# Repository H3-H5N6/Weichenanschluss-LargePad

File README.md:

# Beschreibung

Platine, die die Verkabelung vereinfachen kann. Nutzbar, um 12V oder Fahrstrom zu verteilen.

Es können auch mehrere dieser Platinen miteinander verbunden werden.

Auf der Bestückungsseite(Oberseite) liegt der eine Pol oben, der andere oben.

Auf der Unterseite liegen die beiden Pole jeweils nebeneinander.

# Schaltplan

# Bestückungsplan

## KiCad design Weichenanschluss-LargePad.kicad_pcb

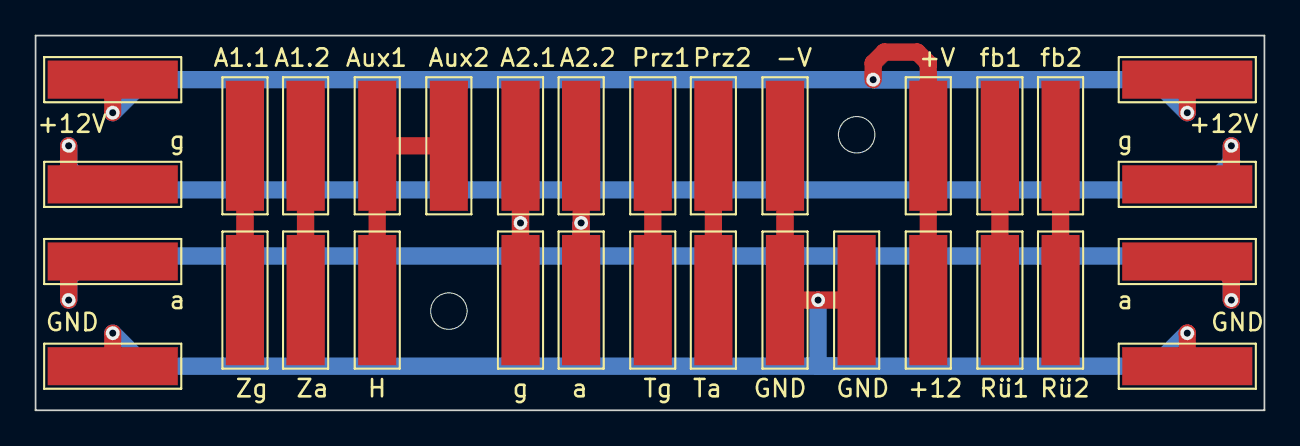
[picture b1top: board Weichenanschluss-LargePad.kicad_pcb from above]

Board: 2 copper layers, 70.8 x 21.6 mm, 36 parts (0 on the bottom side), 11 nets.

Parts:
H1, H3: MountingHole; MountingHole_2.1mm
J1: A1.1; Pad_7.5x2.2mm
J2: A1.2; Pad_7.5x2.2mm
J3: Aux1; Pad_7.5x2.2mm
J4: Aux2; Pad_7.5x2.2mm
J5: A2.1; Pad_7.5x2.2mm
J6: A2.2; Pad_7.5x2.2mm
J7: Prz1; Pad_7.5x2.2mm
J8: Prz2; Pad_7.5x2.2mm
J9: -V; Pad_7.5x2.2mm
J11: +V; Pad_7.5x2.2mm
J12: fb1; Pad_7.5x2.2mm
J13: fb2; Pad_7.5x2.2mm
J21: Zg; Pad_7.5x2.2mm
J22: Za; Pad_7.5x2.2mm
J23: H; Pad_7.5x2.2mm
J25, J41, J51: g; Pad_7.5x2.2mm
J26, J42, J52: a; Pad_7.5x2.2mm
J27: Tg; Pad_7.5x2.2mm
J28: Ta; Pad_7.5x2.2mm
J29, J30, J44, J54: GND; Pad_7.5x2.2mm
J31: +12; Pad_7.5x2.2mm
J32: Rü1; Pad_7.5x2.2mm
J33: Rü2; Pad_7.5x2.2mm
J43, J53: +12V; Pad_7.5x2.2mm
Tx1: ©H3-H5N6; Text
Tx2: Weichenanschluss-LargePad v1.1; Text

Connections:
+12V: J11.1 (Pin_1_1), J31.1 (Pin_1_1), J43.1 (Pin_1_1), J53.1 (Pin_1_1)
GND: J9.1 (Pin_1_1), J29.1 (Pin_1_1), J30.1 (Pin_1_1), J44.1 (Pin_1_1), J54.1 (Pin_1_1)
unnamed: J1.1 (Pin_1_1), J21.1 (Pin_1_1)
unnamed: J2.1 (Pin_1_1), J22.1 (Pin_1_1)
unnamed: J12.1 (Pin_1_1), J32.1 (Pin_1_1)
unnamed: J13.1 (Pin_1_1), J33.1 (Pin_1_1)
unnamed: J3.1 (Pin_1_1), J4.1 (Pin_1_1), J23.1 (Pin_1_1)
unnamed: J5.1 (Pin_1_1), J25.1 (Pin_1_1), J41.1 (Pin_1_1), J51.1 (Pin_1_1)
unnamed: J6.1 (Pin_1_1), J26.1 (Pin_1_1), J42.1 (Pin_1_1), J52.1 (Pin_1_1)
unnamed: J7.1 (Pin_1_1), J27.1 (Pin_1_1)
unnamed: J8.1 (Pin_1_1), J28.1 (Pin_1_1)

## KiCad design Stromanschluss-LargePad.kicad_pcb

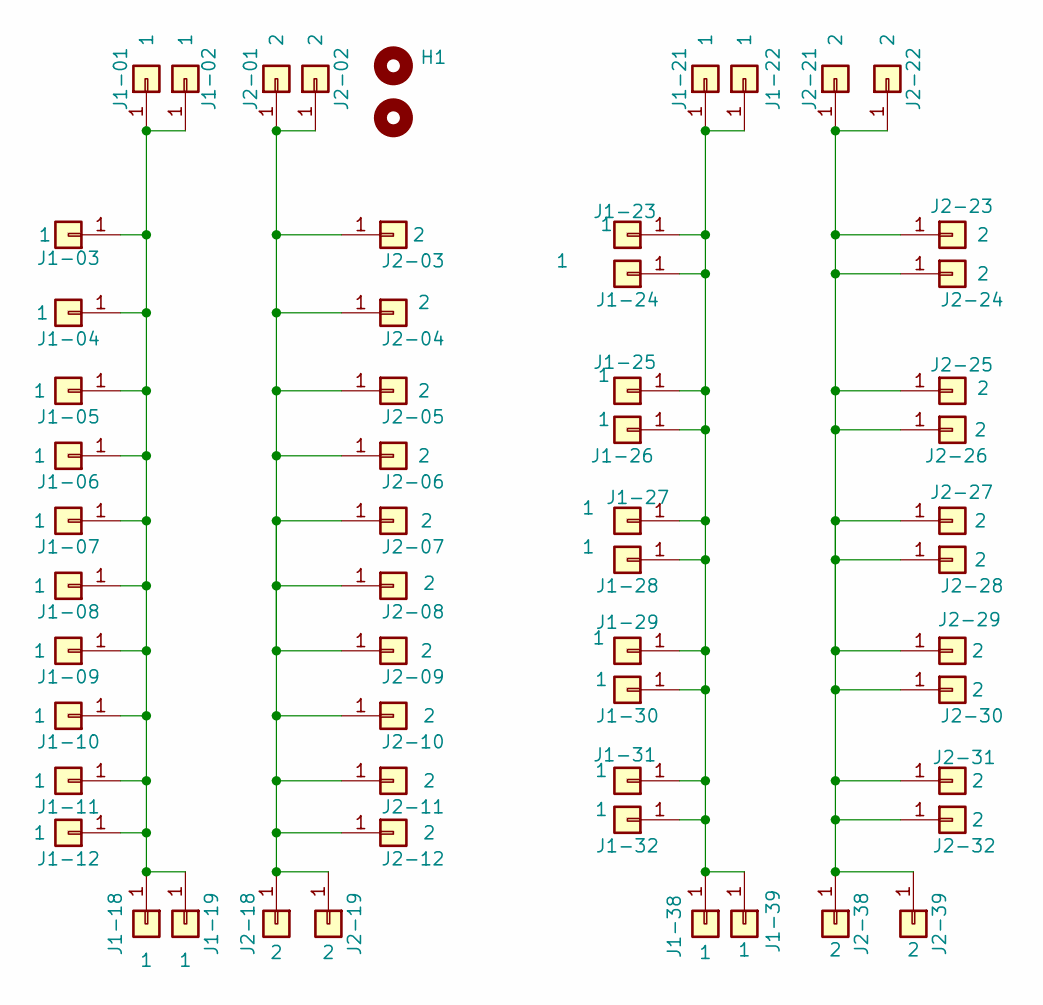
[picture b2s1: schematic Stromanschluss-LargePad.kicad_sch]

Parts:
H1, H3: MountingHole; MountingHole_2.1mm
J1-01, J1-02, J1-03, J1-04, J1-05, J1-06, J1-07, J1-08, J1-09, J1-10, J1-11, J1-12, J1-18, J1-19, J1-21, J1-22, J1-23, J1-24, J1-25, J1-26, J1-27, J1-28, J1-29, J1-30, J1-31, J1-32, J1-38, J1-39: 1; Pad_7.5x2.2mm
J2-01, J2-02, J2-03, J2-04, J2-05, J2-06, J2-07, J2-08, J2-09, J2-10, J2-11, J2-12, J2-18, J2-19, J2-21, J2-22, J2-23, J2-24, J2-25, J2-26, J2-27, J2-28, J2-29, J2-30, J2-31, J2-32, J2-38, J2-39: 2; Pad_7.5x2.2mm

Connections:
unnamed: J1-01.1, J1-02.1, J1-03.1, J1-04.1, J1-05.1, J1-06.1, J1-07.1, J1-08.1, J1-09.1, J1-10.1, J1-11.1, J1-12.1, J1-18.1, J1-19.1
unnamed: J1-21.1, J1-22.1, J1-23.1, J1-24.1, J1-25.1, J1-26.1, J1-27.1, J1-28.1, J1-29.1, J1-30.1, J1-31.1, J1-32.1, J1-38.1, J1-39.1
unnamed: J2-01.1, J2-02.1, J2-03.1, J2-04.1, J2-05.1, J2-06.1, J2-07.1, J2-08.1, J2-09.1, J2-10.1, J2-11.1, J2-12.1, J2-18.1, J2-19.1
unnamed: J2-21.1, J2-22.1, J2-23.1, J2-24.1, J2-25.1, J2-26.1, J2-27.1, J2-28.1, J2-29.1, J2-30.1, J2-31.1, J2-32.1, J2-38.1, J2-39.1

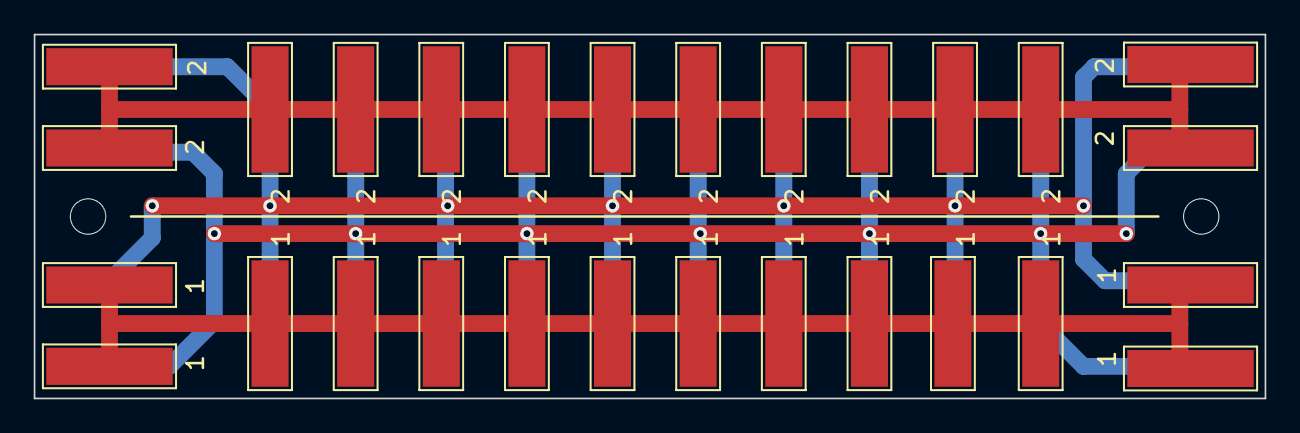
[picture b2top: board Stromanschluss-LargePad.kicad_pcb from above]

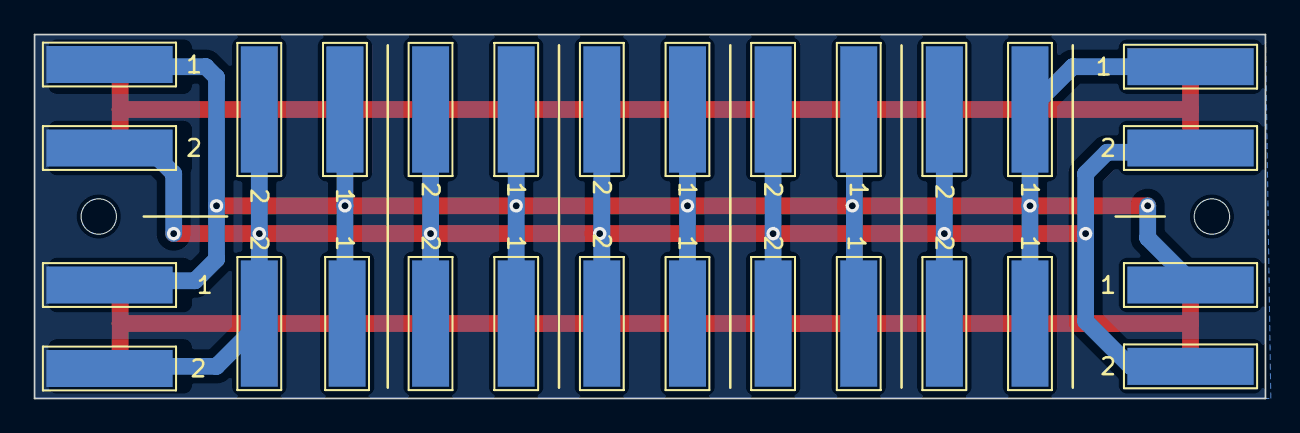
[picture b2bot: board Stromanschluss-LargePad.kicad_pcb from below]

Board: 2 copper layers, 73.0 x 21.6 mm, 58 parts (28 on the bottom side), 4 nets.

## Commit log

2024-01-24 Initial
2024-01-24 Dokumentetation hinzugefügt
2025-02-28 Aktueller Arbeitsstand
2025-02-28 Backup-Ordner angepasst
2026-04-09 Kicad 10
2026-04-10 Bilder von Antrieb und Beschaltung der Weiche hinzugefügt
2026-04-10 .gitignore um tmp erweitert
2026-04-10 Name der Pad-Footprints angepasst: Wago->Connector_Misc
